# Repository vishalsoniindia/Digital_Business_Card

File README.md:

# Digital_Business_Card
In this repo we gonna learn how to perform HID with Attiny85, Also we will make a Digital business card based on Squid Games Theme. I have used Digispark board which can be used to make rubber ducky.

Watch Video :- https://youtu.be/2BLEFzPEG6Y

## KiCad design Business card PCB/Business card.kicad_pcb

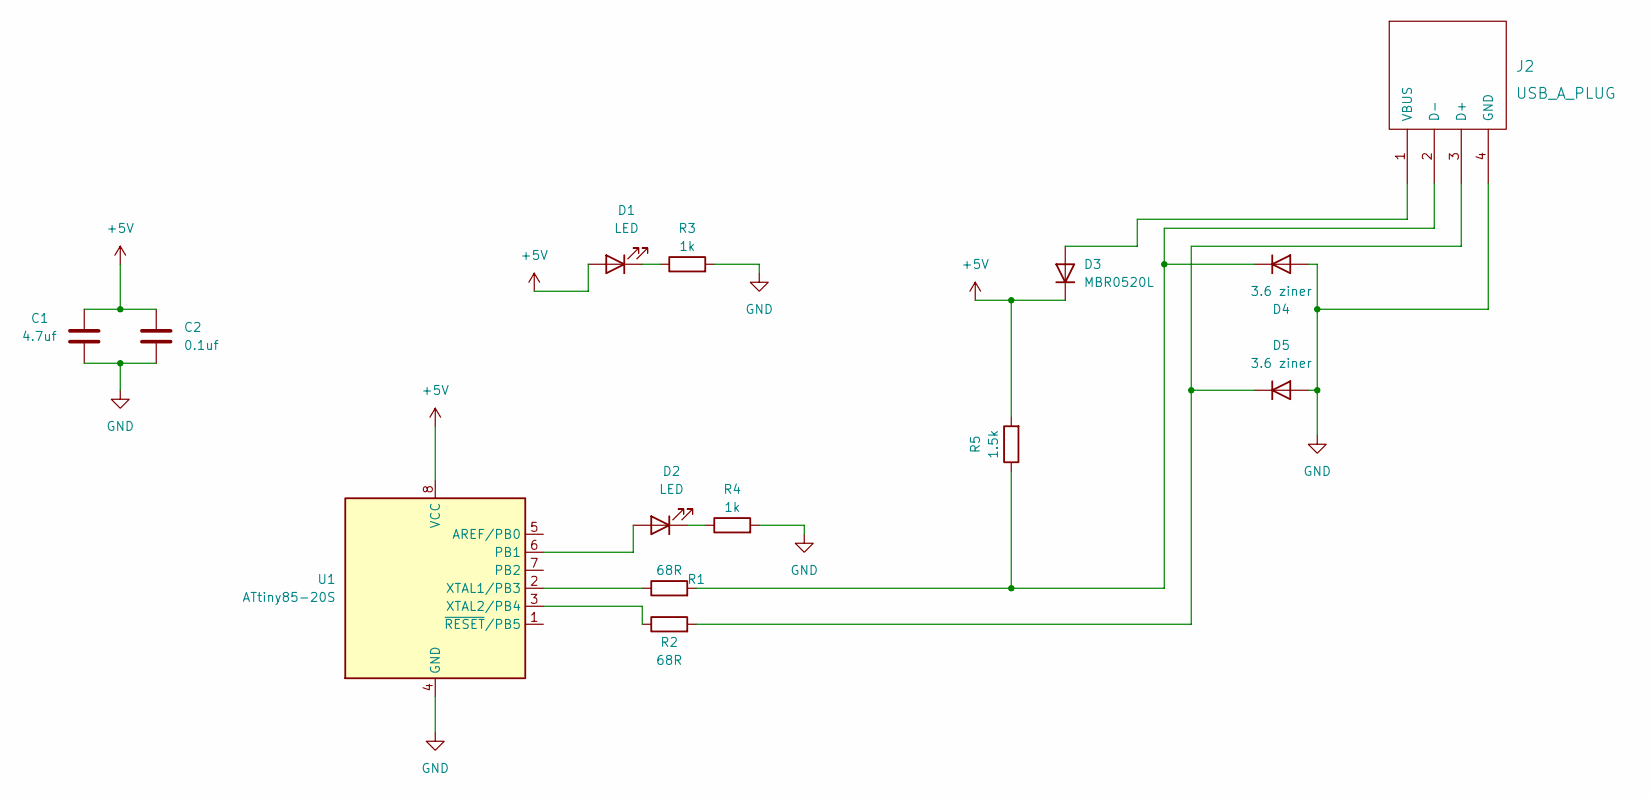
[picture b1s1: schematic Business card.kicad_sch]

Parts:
C1: 4.7uf; C_0805_2012Metric_Pad1.18x1.45mm_HandSolder
C2: 0.1uf; C_0603_1608Metric_Pad1.08x0.95mm_HandSolder
D1, D2: LED; LED_0603_1608Metric_Pad1.05x0.95mm_HandSolder
D3: MBR0520L; D_1206_3216Metric_Pad1.42x1.75mm_HandSolder
D4, D5: 3.6 ziner; D_0805_2012Metric_Pad1.15x1.40mm_HandSolder
J2: USB_A_PLUG; usb-PCB
R1, R2: 68R; R_0603_1608Metric_Pad0.98x0.95mm_HandSolder
R3, R4: 1k; R_0603_1608Metric_Pad0.98x0.95mm_HandSolder
R5: 1.5k; R_0603_1608Metric_Pad0.98x0.95mm_HandSolder
U1: ATtiny85-20S; SOIC-8W_5.3x5.3mm_P1.27mm

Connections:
+5V: C1.1, C2.1, D1.2 (A), D3.2 (K), R5.2, U1.8 (VCC)
GND: C1.2, C2.2, D4.1 (A), D5.1 (A), J2.4 (GND), R3.2, R4.2, U1.4 (GND)
unnamed: D1.1 (K), R3.1
unnamed: D2.1 (K), R4.1
unnamed: D2.2 (A), U1.6 (PB1)
unnamed: D3.1 (A), J2.1 (VBUS)
unnamed: D4.2 (K), J2.2 (D-), R1.2, R5.1
unnamed: D5.2 (K), J2.3 (D+), R2.2
unnamed: R1.1, U1.2 (XTAL1/PB3)
unnamed: R2.1, U1.3 (XTAL2/PB4)

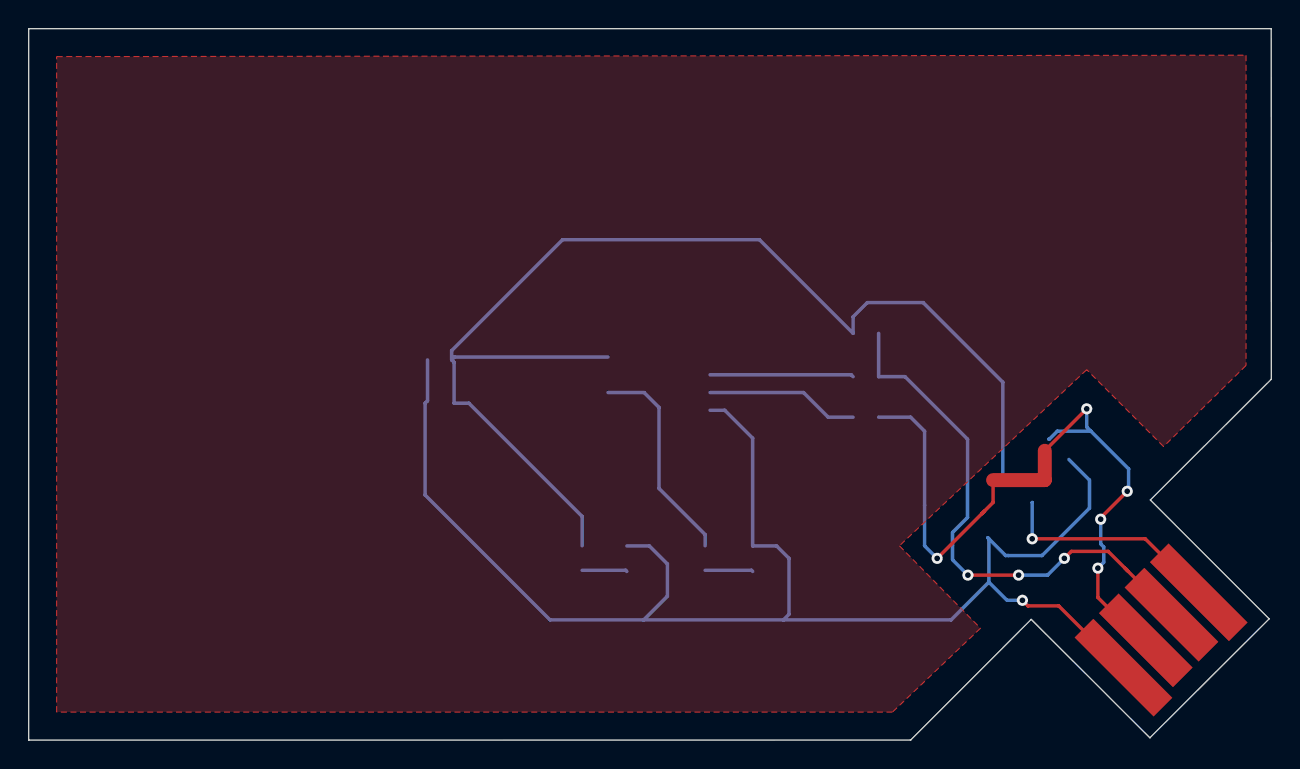
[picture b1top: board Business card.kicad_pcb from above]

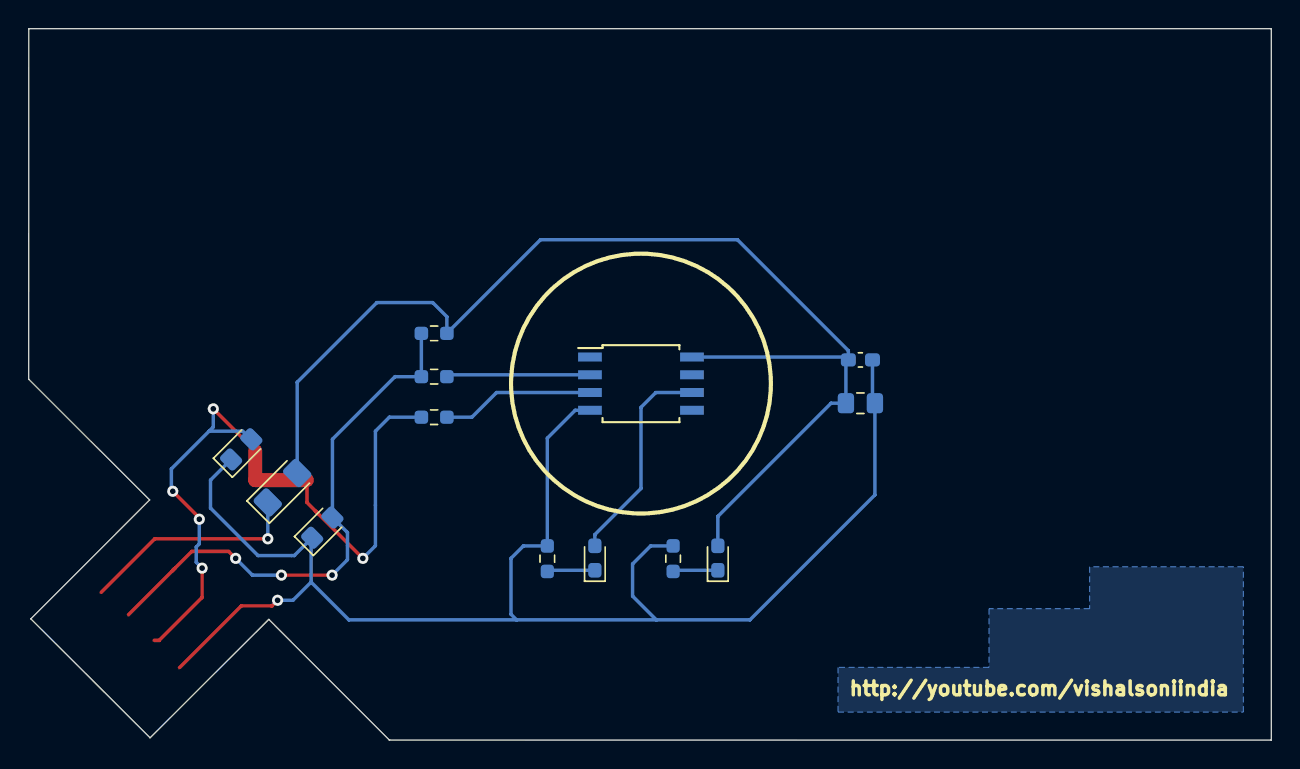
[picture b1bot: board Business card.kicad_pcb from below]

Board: 2 copper layers, 88.9 x 50.9 mm, 14 parts (13 on the bottom side), 10 nets.
